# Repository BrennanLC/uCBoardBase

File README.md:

uCBoardBase
===========

Microcontroller breakout board built with the Texas Instruments TM4C123BE6PM.

Design has not yet been verified. Build at your own risk!

Files:

uCBoardBase.pdf - Copy of board schematic in PDF format
uCBoardBase.sch - Board schematic eagle file 
uCBoardBase.brd - Board layout eagle file
uCBoardBaseBoard.pdf - Board layout in PDF format

schematic and board layout built with Eagle 6.4.0 Standard. More info and 
download available here:

https://www.cadsoftusa.com/

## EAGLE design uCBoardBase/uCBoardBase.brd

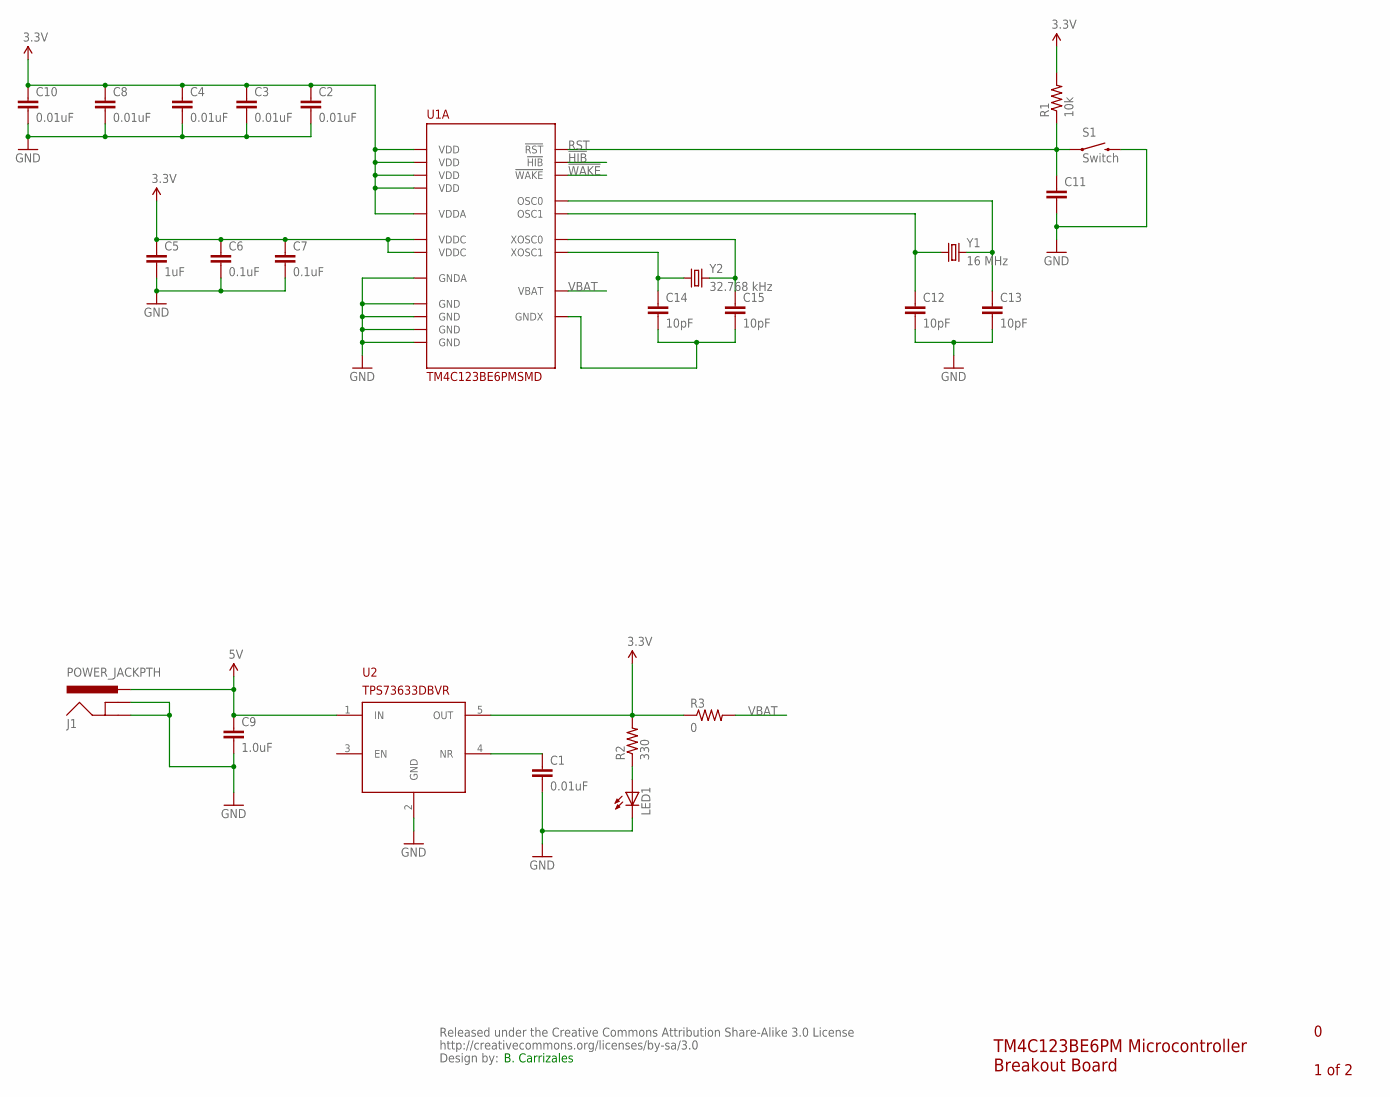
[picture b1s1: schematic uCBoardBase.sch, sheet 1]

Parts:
C1, C2, C3, C4, C8, C10: 0.01uF; 0603-CAP
C5: 1uF; 0603-CAP
C6, C7: 0.1uF; 0603-CAP
C9: 1.0uF; 0603-CAP
C11: CAP0603-CAP; 0603-CAP
C12, C13, C14, C15: 10pF; 0603-CAP
CC_TEXT1: CREATIVE_COMMONS
J1: POWER_JACKPTH; POWER_JACK_PTH
LED1: LED1206; LED-1206
R1: 10k; 0603-RES
R2: 330; 0603-RES
R3: 0; 0603-RES
S1: Switch; TACTILE-SWITCH-1101NE
U1: TM4C123BE6PMSMD; 64LQFP
U2: TPS73633DBVR; SOT23-DBV
Y1: 16 MHz; HC49US
Y2: 32.768 kHz; TC26H

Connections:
3.3V: C2.1, C3.1, C4.1, C5.1, C6.1, C7.1, C8.1, C10.1, R1.2, R2.2, R3.1, U1.2 (VDDA), U1.11 (VDD), U1.25 (VDDC), U1.26 (VDD), U1.42 (VDD), U1.54 (VDD), U1.56 (VDDC), U2.5 (OUT); also elsewhere on the board
5V: C9.1, J1.PWR, U2.1 (IN); also elsewhere on the board
!HIB: U1.33 (!HIB); also elsewhere on the board
!WAKE: U1.32 (!WAKE); also elsewhere on the board
GND: C1.2, C2.2, C3.2, C4.2, C5.2, C6.2, C7.2, C8.2, C9.2, C10.2, C11.2, C12.2, C13.2, J1.GND, J1.GNDBREAK, LED1.C, S1.P$2 (2), U1.3 (GNDA), U1.12 (GND), U1.27 (GND), U1.39 (GND), U1.55 (GND), U2.2 (GND); also elsewhere on the board
unnamed: C13.1, U1.40 (OSC0), Y1.2
unnamed: C12.1, U1.41 (OSC1), Y1.1
unnamed: C1.1, U2.4 (NR)
unnamed: LED1.A, R2.1
unnamed: C14.1, U1.36 (XOSC1), Y2.1
unnamed: C15.1, U1.34 (XOSC0), Y2.2
unnamed: C14.2, C15.2, U1.35 (GNDX)
RST: C11.1, R1.1, S1.P$1 (1), U1.38 (!RST); also elsewhere on the board
VBAT: R3.2, U1.37 (VBAT); also elsewhere on the board

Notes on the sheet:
TM4C123BE6PM Microcontroller Breakout Board
1 of 2
B. Carrizales

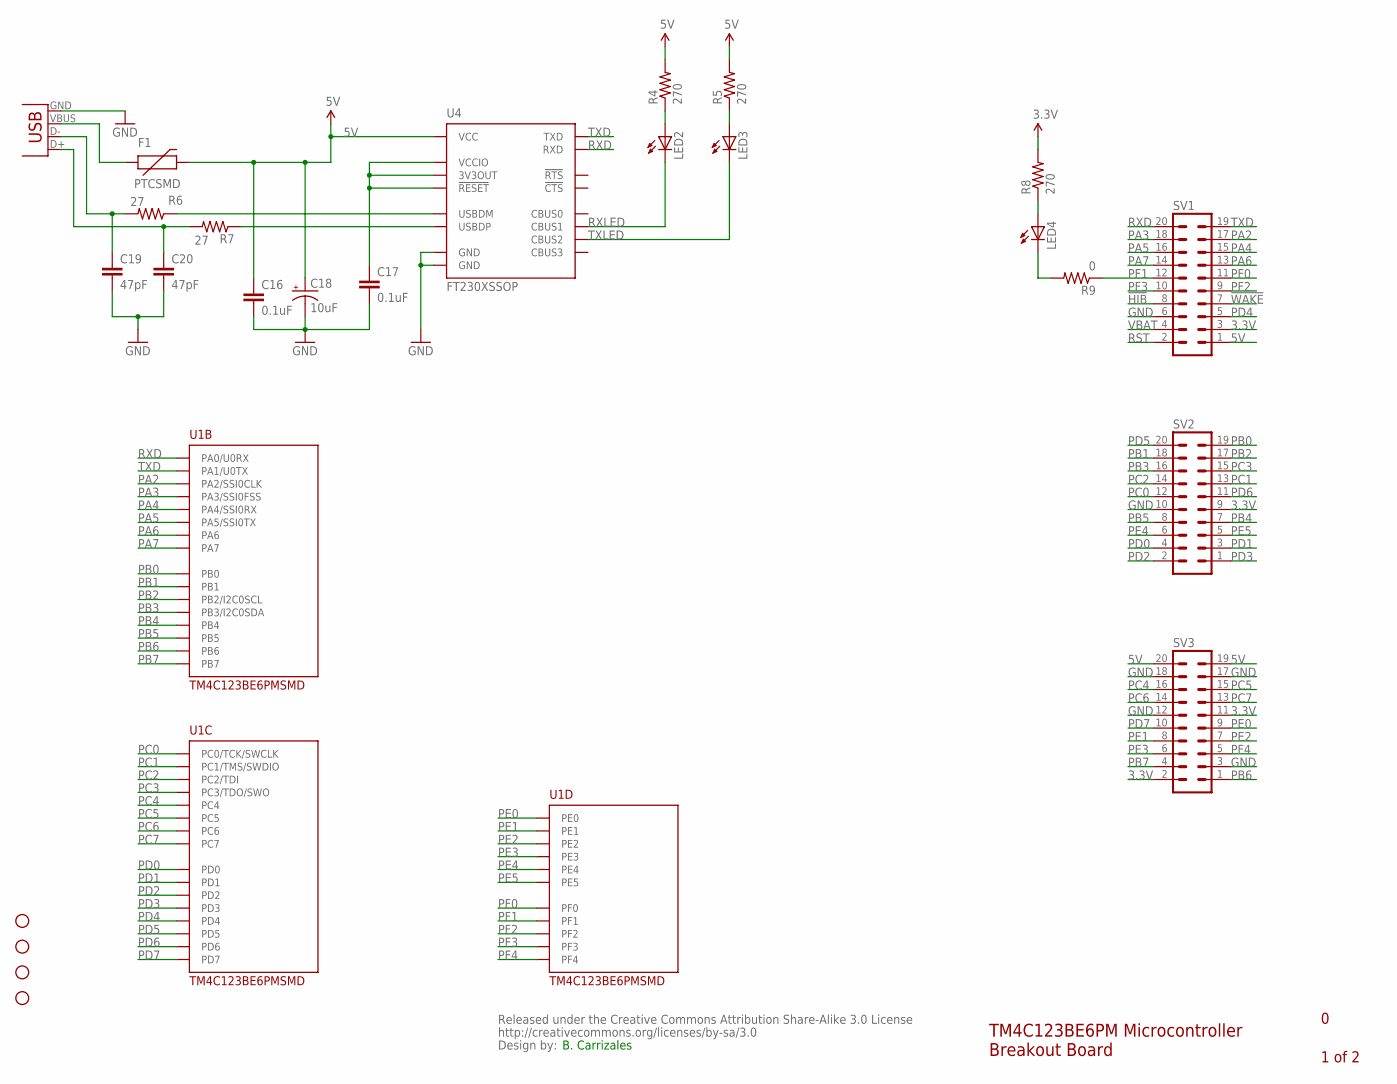
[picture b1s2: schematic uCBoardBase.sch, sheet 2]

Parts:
C16, C17: 0.1uF; 0603-CAP
C18: 10uF; EIA3216-KIT
C19, C20: 47pF; 0603-CAP
CC_TEXT2: CREATIVE_COMMONS
F1: PTCSMD; PTC-1206
JP2: USBSMD; USB-MINIB
LED2, LED3, LED4: LED0603; LED-0603
R4, R5, R8: 270; 0603-RES
R6, R7: 27; 0603-RES
R9: 0; 0603-RES
STANDOFF1, STANDOFF2, STANDOFF3, STANDOFF4: STAND-OFF
SV1, SV2, SV3: MA10-2
U1: TM4C123BE6PMSMD; 64LQFP
U4: FT230XSSOP; SSOP16

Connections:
3.3V: R8.2, SV1.3, SV2.9, SV3.2, SV3.11; also elsewhere on the board
5V: C16.1, C18.A (+), F1.2, R4.2, R5.2, SV1.1, SV3.19, SV3.20, U4.12 (VCC); also elsewhere on the board
!HIB: SV1.8; also elsewhere on the board
!WAKE: SV1.7; also elsewhere on the board
GND: C16.2, C17.2, C18.C (-), C19.2, C20.2, JP2.GND, SV1.6, SV2.10, SV3.3, SV3.12, SV3.17, SV3.18, U4.5 (GND), U4.13 (GND); also elsewhere on the board
unnamed: LED4.A, R8.1
unnamed: C19.1, JP2.D-, R6.2
unnamed: C20.1, JP2.D+, R7.2
unnamed: LED3.A, R5.1
unnamed: LED2.A, R4.1
unnamed: F1.1, JP2.VBUS
unnamed: R7.1, U4.8 (USBDP)
unnamed: R6.1, U4.9 (USBDM)
unnamed: C17.1, U4.3 (VCCIO), U4.10 (3V3OUT), U4.11 (!RESET)
PA2: SV1.17, U1.19 (PA2/SSI0CLK)
PA3: SV1.18, U1.20 (PA3/SSI0FSS)
PA4: SV1.15, U1.21 (PA4/SSI0RX)
PA5: SV1.16, U1.22 (PA5/SSI0TX)
PA6: SV1.13, U1.23 (PA6)
PA7: SV1.14, U1.24 (PA7)
PB0: SV2.19, U1.45 (PB0)
PB1: SV2.18, U1.46 (PB1)
PB2: SV2.17, U1.47 (PB2/I2C0SCL)
PB3: SV2.16, U1.48 (PB3/I2C0SDA)
PB4: SV2.7, U1.58 (PB4)
PB5: SV2.8, U1.57 (PB5)
PB6: SV3.1, U1.1 (PB6)
PB7: SV3.4, U1.4 (PB7)
PC0: SV2.12, U1.52 (PC0/TCK/SWCLK)
PC1: SV2.13, U1.51 (PC1/TMS/SWDIO)
PC2: SV2.14, U1.50 (PC2/TDI)
PC3: SV2.15, U1.49 (PC3/TDO/SWO)
PC4: SV3.16, U1.16 (PC4)
PC5: SV3.15, U1.15 (PC5)
PC6: SV3.14, U1.14 (PC6)
PC7: SV3.13, U1.13 (PC7)
PD0: SV2.4, U1.61 (PD0)
PD1: SV2.3, U1.62 (PD1)
PD2: SV2.2, U1.63 (PD2)
PD3: SV2.1, U1.64 (PD3)
PD4: SV1.5, U1.43 (PD4)
PD5: SV2.20, U1.44 (PD5)
PD6: SV2.11, U1.53 (PD6)
PD7: SV3.10, U1.10 (PD7)
PE0: SV3.9, U1.9 (PE0)
PE1: SV3.8, U1.8 (PE1)
PE2: SV3.7, U1.7 (PE2)
PE3: SV3.6, U1.6 (PE3)
PE4: SV2.6, U1.59 (PE4)
PE5: SV2.5, U1.60 (PE5)
PF0: SV1.11, U1.28 (PF0)
PF1: R9.1, SV1.12, U1.29 (PF1)
PF2: SV1.9, U1.30 (PF2)
PF3: SV1.10, U1.31 (PF3)
PF4: SV3.5, U1.5 (PF4)
RST: SV1.2; also elsewhere on the board
RXD: SV1.20, U1.17 (PA0/U0RX), U4.4 (RXD)
RXLED: LED2.C, U4.14 (CBUS1)
TXD: SV1.19, U1.18 (PA1/U0TX), U4.1 (TXD)
TXLED: LED3.C, U4.7 (CBUS2)
TXLED1: LED4.C, R9.2
VBAT: SV1.4; also elsewhere on the board

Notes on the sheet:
1 of 2
TM4C123BE6PM Microcontroller Breakout Board
B. Carrizales

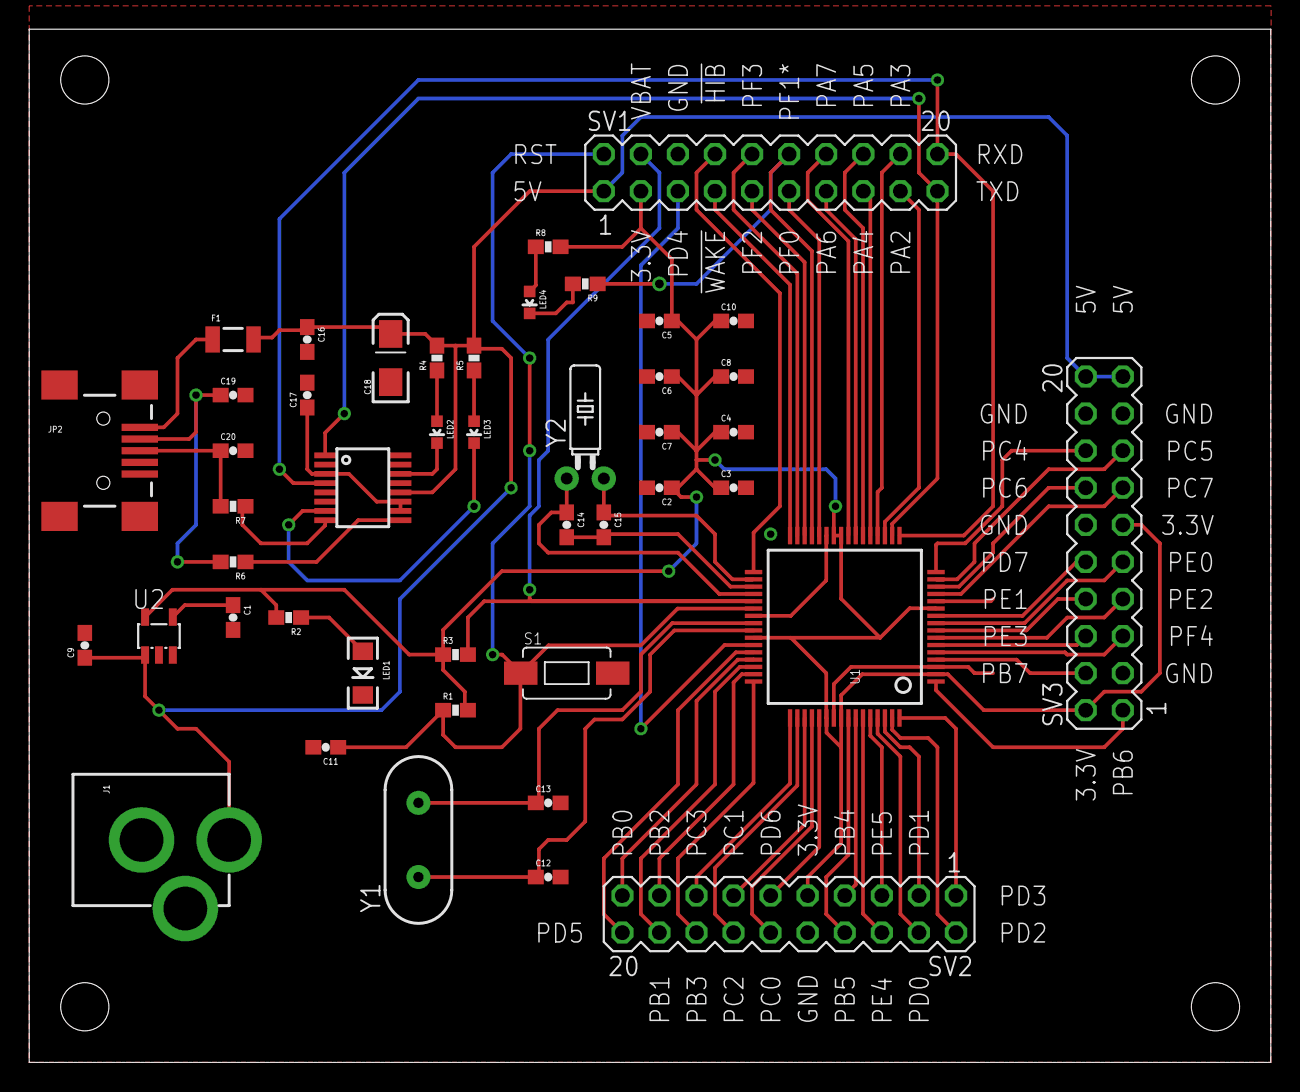
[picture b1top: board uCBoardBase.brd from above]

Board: 2 copper layers, 85.1 x 70.8 mm, 51 parts (0 on the bottom side), 69 nets.

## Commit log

2013-11-08 Added Schematic
    Added schematic of uCBoardBase
2013-11-11 Updated Schematic
    Updated schematic
2013-11-28 Updated Schematic and Layout
    Updated schematic and finished board layout
2014-02-27 Updated PDF Files

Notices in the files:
parts and their libraries:
SparkFun-Passives: Licensing: CC v3.0 Share-Alike You are welcome to use this library for commercial purposes.
SparkFun-Aesthetics: Released under the Creative Commons Attribution Share-Alike 3.0 License
SparkFun-Aesthetics: http://creativecommons.org/licenses/by-sa/3.0
